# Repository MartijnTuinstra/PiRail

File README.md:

# PiRail
Raspberry Pi Rail Software

This software package is for a modeltrain enthusiasts that want to automate trains on their layout.
It is especially created for club layout that do not have specified order.

This package contains
- Board designs
- Firmware for the arduino's
- Software Engine
- Web interface
- Z21 Emulator & firmware for arduino

# Requirements

## Hardware

- 100MB storage space
- 100MB min RAM size
- 1GHz 2core ARM or better adviced

- Z21 Command Unit
- A Railway
- DCC trains

## Software

- PHP5
- wiringPi
- openssl

# Installation and Configuration

To build all the binaries and launch the Engine:
```
make
./baan
```

Use the config\_reader to edit or create modules
```
./config\_reader
```

To build and launch the Emulator:
```
cd Z21_Emulator
gcc emulator.c -std=c99 -lpthread -g -o Z21.out
./Z21.out
```

# Web interface

Make sure to drop the 'web' folder into your webserver. This package has no php webserver.

Browse to the index.php. This is the main interface.
From here you can:
- add/change train and so called Modules
- Control trains
- Control the layout

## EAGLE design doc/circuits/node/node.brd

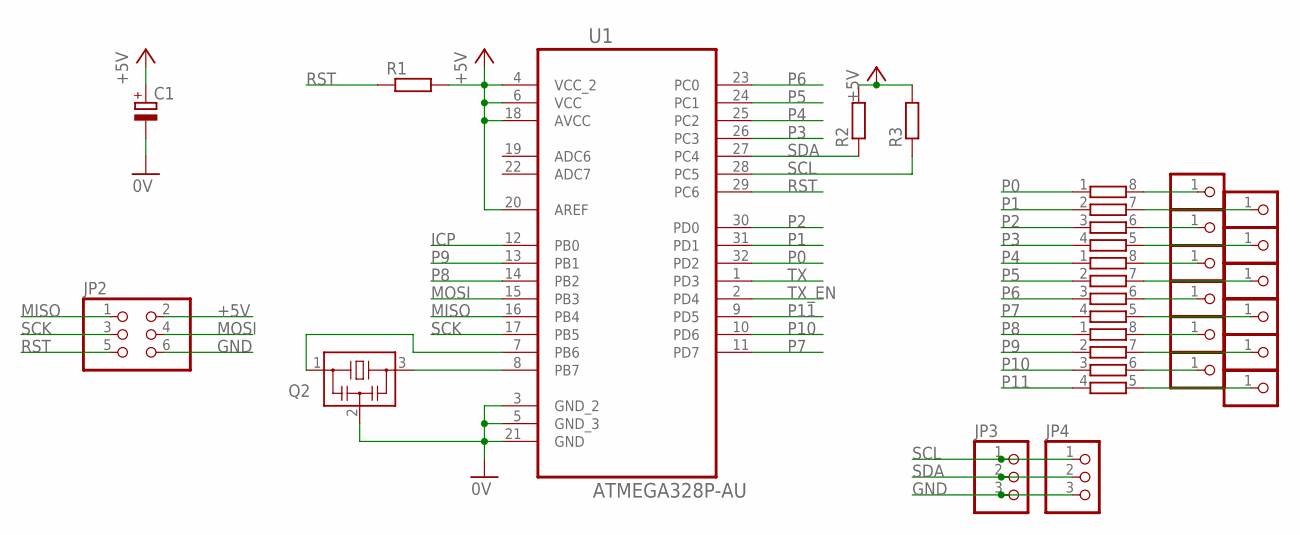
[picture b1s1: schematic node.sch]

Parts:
C1: CPOL-EU153CLV-0405; 153CLV-0405
JP1, JP6, JP7, JP8, JP9, JP10, JP11, JP12, JP13, JP14, JP15, JP16: PINHD-1X1; 1X01
JP2: PINHD-2X3; 2X03
JP3, JP4: PINHD-1X3; 1X03
Q2: CSTCR6M00G53Z; CSTCR6M
R1, R2, R3: R-EU_R0402; R0402
RN1, RN2, RN3: 4R-NEXB28V; EXB28V
U1: ATMEGA328P-AU; QFP80P900X900X120-32N

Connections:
+5V: C1.+, JP2.2, R1.2, R2.2, R3.2, U1.4 (VCC_2), U1.6 (VCC), U1.18 (AVCC), U1.20 (AREF)
GND: C1.-, JP2.6, JP3.3, JP4.3, Q2.2, U1.3 (GND_2), U1.5 (GND_3), U1.21 (GND)
ICP: U1.12 (PB0)
MISO: JP2.1, U1.16 (PB4)
MOSI: JP2.4, U1.15 (PB3)
unnamed: Q2.3, U1.8 (PB7)
unnamed: Q2.1, U1.7 (PB6)
unnamed: JP1.1, RN1.8 (2)
unnamed: JP16.1, RN1.7 (2)
unnamed: JP6.1, RN1.6 (2)
unnamed: JP15.1, RN1.5 (2)
unnamed: JP7.1, RN2.8 (2)
unnamed: JP14.1, RN2.7 (2)
unnamed: JP8.1, RN2.6 (2)
unnamed: JP13.1, RN2.5 (2)
unnamed: JP9.1, RN3.8 (2)
unnamed: JP12.1, RN3.7 (2)
unnamed: JP10.1, RN3.6 (2)
unnamed: JP11.1, RN3.5 (2)
P0: RN1.1, U1.32 (PD2)
P1: RN1.2 (1), U1.31 (PD1)
P2: RN1.3 (1), U1.30 (PD0)
P3: RN1.4 (1), U1.26 (PC3)
P4: RN2.1, U1.25 (PC2)
P5: RN2.2 (1), U1.24 (PC1)
P6: RN2.3 (1), U1.23 (PC0)
P7: RN2.4 (1), U1.11 (PD7)
P8: RN3.1, U1.14 (PB2)
P9: RN3.2 (1), U1.13 (PB1)
P10: RN3.3 (1), U1.10 (PD6)
P11: RN3.4 (1), U1.9 (PD5)
RST: JP2.5, R1.1, U1.29 (PC6)
SCK: JP2.3, U1.17 (PB5)
SCL: JP3.1, JP4.1, R3.1, U1.28 (PC5)
SDA: JP3.2, JP4.2, R2.1, U1.27 (PC4)
TX: U1.1 (PD3)
TX_EN: U1.2 (PD4)

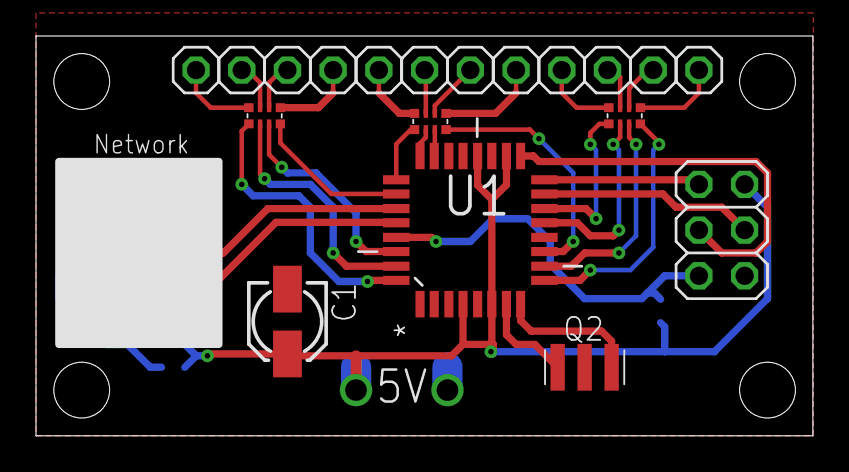
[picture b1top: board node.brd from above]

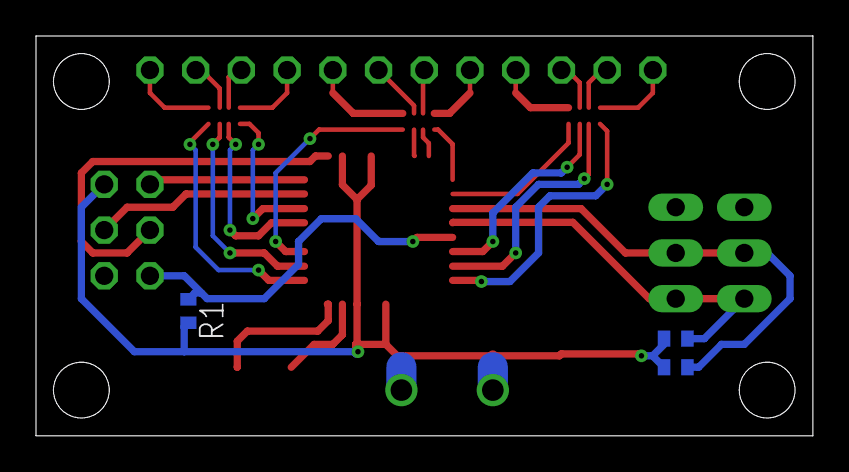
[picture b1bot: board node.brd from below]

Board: 2 copper layers, 43.2 x 22.2 mm, 24 parts (3 on the bottom side), 34 nets.

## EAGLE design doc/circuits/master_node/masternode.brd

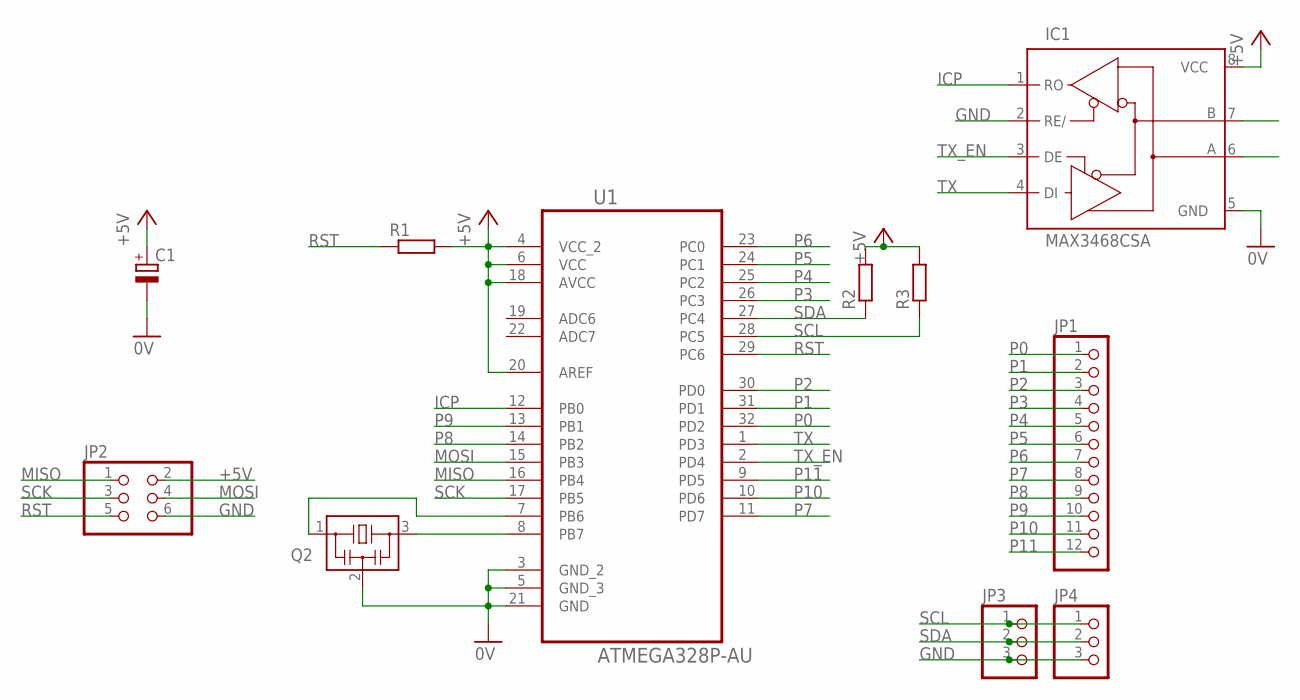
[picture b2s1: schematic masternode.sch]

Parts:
C1: CPOL-EU153CLV-0405; 153CLV-0405
IC1: MAX3468CSA; SO08
JP1: PINHD-1X12; 1X12
JP2: PINHD-2X3; 2X03
JP3, JP4: PINHD-1X3; 1X03
Q2: CSTCR6M00G53Z; CSTCR6M
R1, R2, R3: R-EU_R0402; R0402
U1: ATMEGA328P-AU; QFP80P900X900X120-32N

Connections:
+5V: C1.+, IC1.8 (VCC), JP2.2, R1.2, R2.2, R3.2, U1.4 (VCC_2), U1.6 (VCC), U1.18 (AVCC), U1.20 (AREF)
A: IC1.6 (A)
B: IC1.7 (B)
GND: C1.-, IC1.2 (RE/), IC1.5 (GND), JP2.6, JP3.3, JP4.3, Q2.2, U1.3 (GND_2), U1.5 (GND_3), U1.21 (GND)
ICP: IC1.1 (RO), U1.12 (PB0)
MISO: JP2.1, U1.16 (PB4)
MOSI: JP2.4, U1.15 (PB3)
unnamed: Q2.3, U1.8 (PB7)
unnamed: Q2.1, U1.7 (PB6)
P0: JP1.1, U1.32 (PD2)
P1: JP1.2, U1.31 (PD1)
P2: JP1.3, U1.30 (PD0)
P3: JP1.4, U1.26 (PC3)
P4: JP1.5, U1.25 (PC2)
P5: JP1.6, U1.24 (PC1)
P6: JP1.7, U1.23 (PC0)
P7: JP1.8, U1.11 (PD7)
P8: JP1.9, U1.14 (PB2)
P9: JP1.10, U1.13 (PB1)
P10: JP1.11, U1.10 (PD6)
P11: JP1.12, U1.9 (PD5)
RST: JP2.5, R1.1, U1.29 (PC6)
SCK: JP2.3, U1.17 (PB5)
SCL: JP3.1, JP4.1, R3.1, U1.28 (PC5)
SDA: JP3.2, JP4.2, R2.1, U1.27 (PC4)
TX: IC1.4 (DI), U1.1 (PD3)
TX_EN: IC1.3 (DE), U1.2 (PD4)

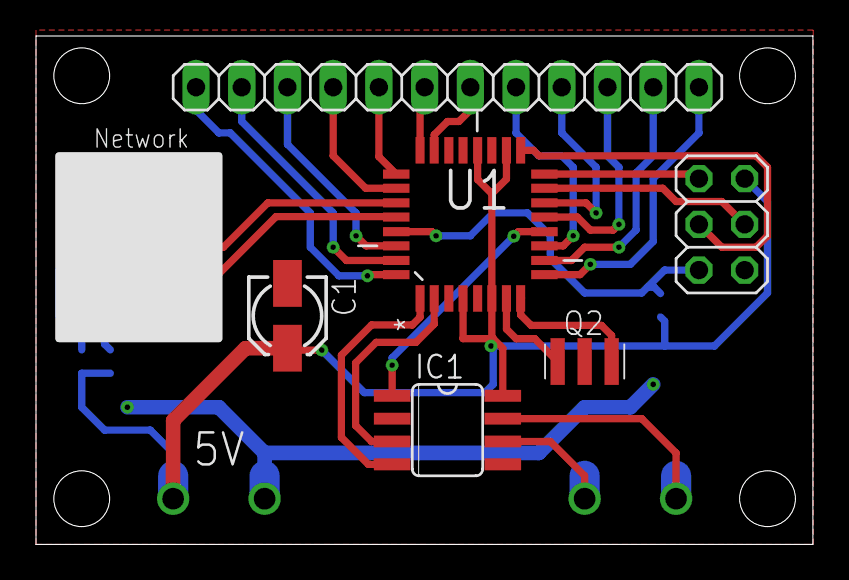
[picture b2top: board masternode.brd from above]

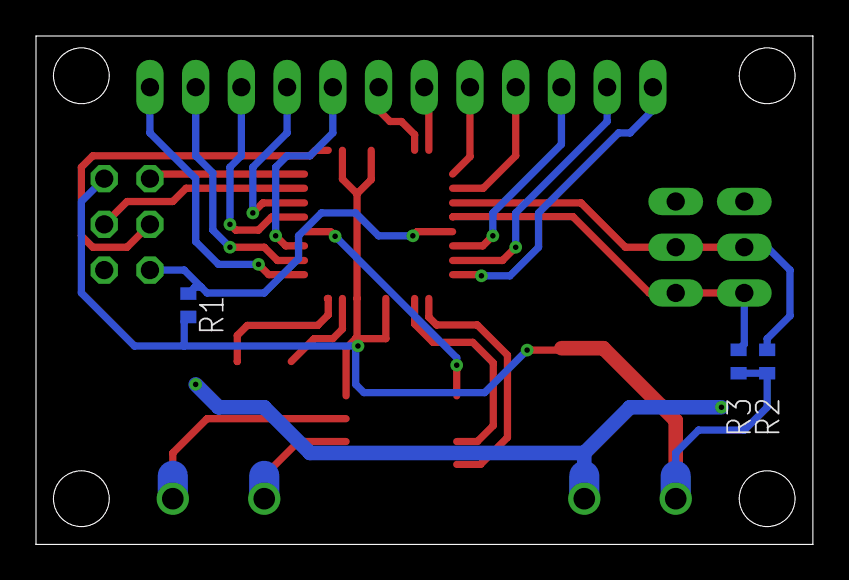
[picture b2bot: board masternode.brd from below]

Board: 2 copper layers, 43.2 x 28.2 mm, 11 parts (3 on the bottom side), 25 nets.

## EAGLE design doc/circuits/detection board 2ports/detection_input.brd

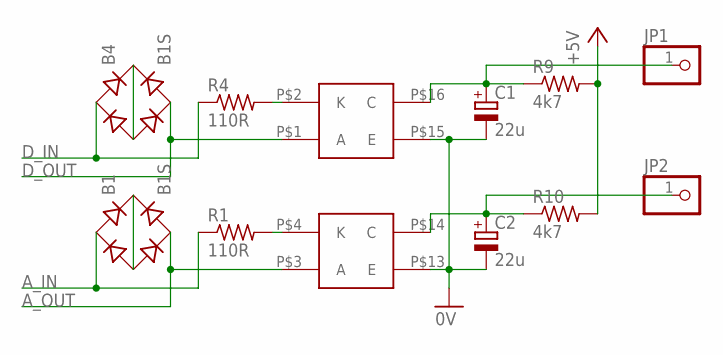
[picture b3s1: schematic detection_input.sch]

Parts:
B1, B4: B1S; MBS
C1, C2: 22u; E2-4
JP1, JP2: PINHD-1X1; 1X01
R1, R4: 110R; R0805
R9, R10: 4k7; R0805
U$1: ILQ620D

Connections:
0V: C1.-, C2.-, U$1.P$13 (E), U$1.P$15 (E)
+5V: R9.2, R10.2
A: C1.+, JP1.1, R9.1, U$1.P$16 (C)
A_IN: B1.AC1, R1.1
A_OUT: B1.AC2, U$1.P$3 (A)
B: C2.+, JP2.1, R10.1, U$1.P$14 (C)
D_IN: B4.AC1, R4.1
D_OUT: B4.AC2, U$1.P$1 (A)
unnamed: B1.+, B1.-
unnamed: R1.2, U$1.P$4 (K)
unnamed: R4.2, U$1.P$2 (K)
unnamed: B4.+, B4.-

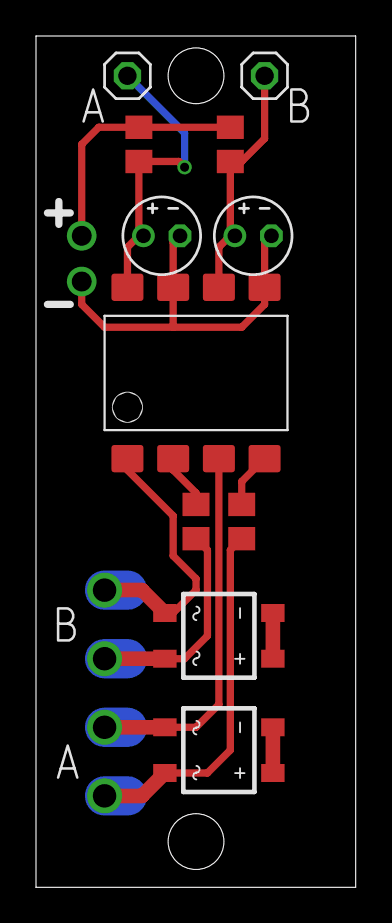
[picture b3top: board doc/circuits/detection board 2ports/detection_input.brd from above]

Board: 2 copper layers, 17.8 x 47.3 mm, 11 parts (0 on the bottom side), 12 nets.

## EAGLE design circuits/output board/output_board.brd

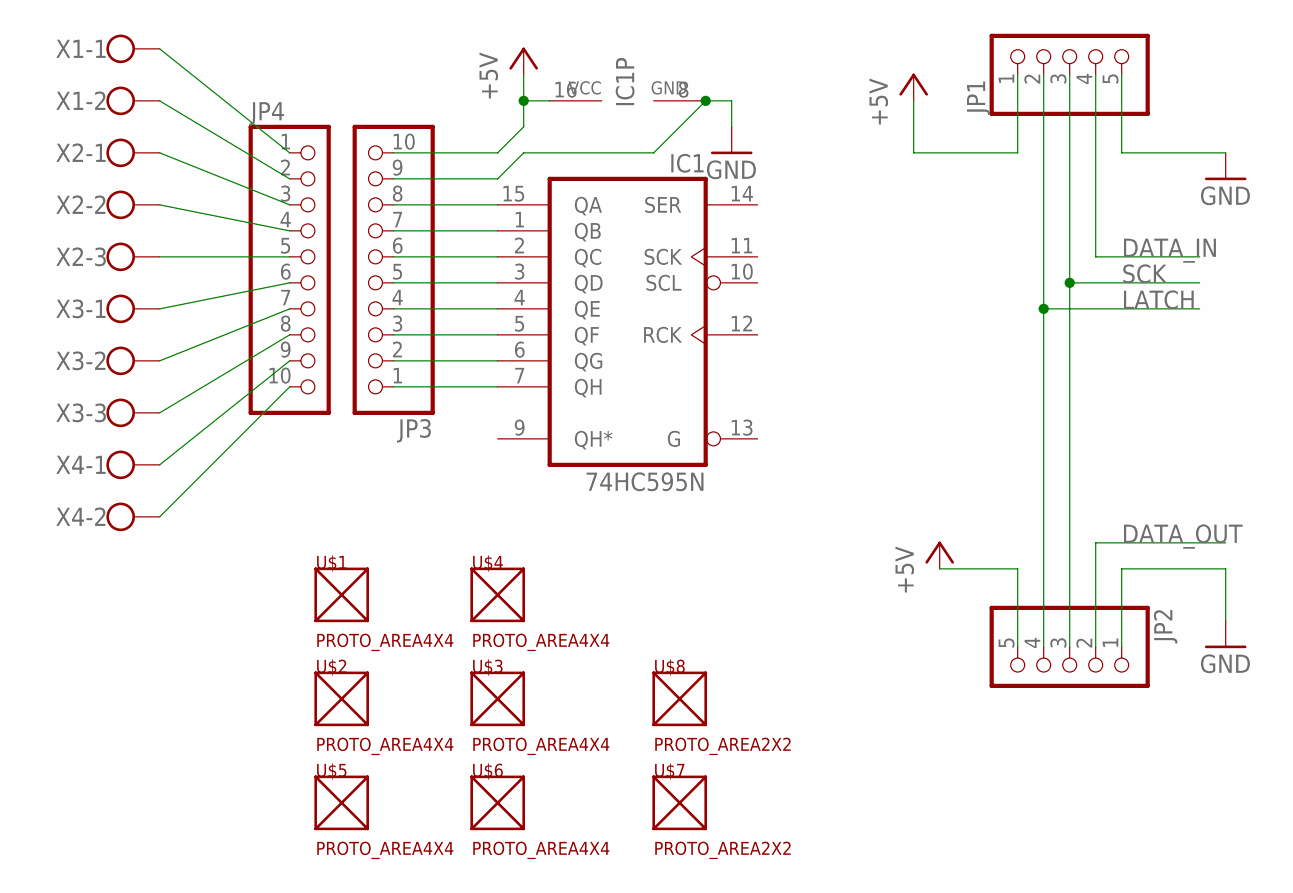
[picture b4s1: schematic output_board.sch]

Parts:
IC1: 74HC595N; DIL16
JP1, JP2: PINHD-1X5; 1X05
JP3, JP4: PINHD-1X10; 1X10
U$1, U$2, U$3, U$4, U$5, U$6: PROTO_AREA4X4; PROTO4X4
U$7, U$8: PROTO_AREA2X2; PROTO2X2
X1, X4: W237-102
X2, X3: W237-103

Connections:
+5V: IC1.16 (VCC), JP1.1, JP2.5, JP3.10
DATA_IN: JP1.4
DATA_OUT: JP2.2
GND: IC1.8 (GND), JP1.5, JP2.1, JP3.9
LATCH: JP1.2, JP2.4
unnamed: IC1.7 (QH), JP3.1
unnamed: IC1.6 (QG), JP3.2
unnamed: IC1.5 (QF), JP3.3
unnamed: IC1.4 (QE), JP3.4
unnamed: IC1.3 (QD), JP3.5
unnamed: IC1.2 (QC), JP3.6
unnamed: IC1.1 (QB), JP3.7
unnamed: IC1.15 (QA), JP3.8
unnamed: JP4.1, X1.1
unnamed: JP4.2, X1.2
unnamed: JP4.3, X2.1
unnamed: JP4.4, X2.2
unnamed: JP4.5, X2.3
unnamed: JP4.6, X3.1
unnamed: JP4.7, X3.2
unnamed: JP4.8, X3.3
unnamed: JP4.9, X4.1
unnamed: JP4.10, X4.2
SCK: JP1.3, JP2.3

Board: 2 copper layers, 17 parts (0 on the bottom side), 22 nets, no tracks yet.

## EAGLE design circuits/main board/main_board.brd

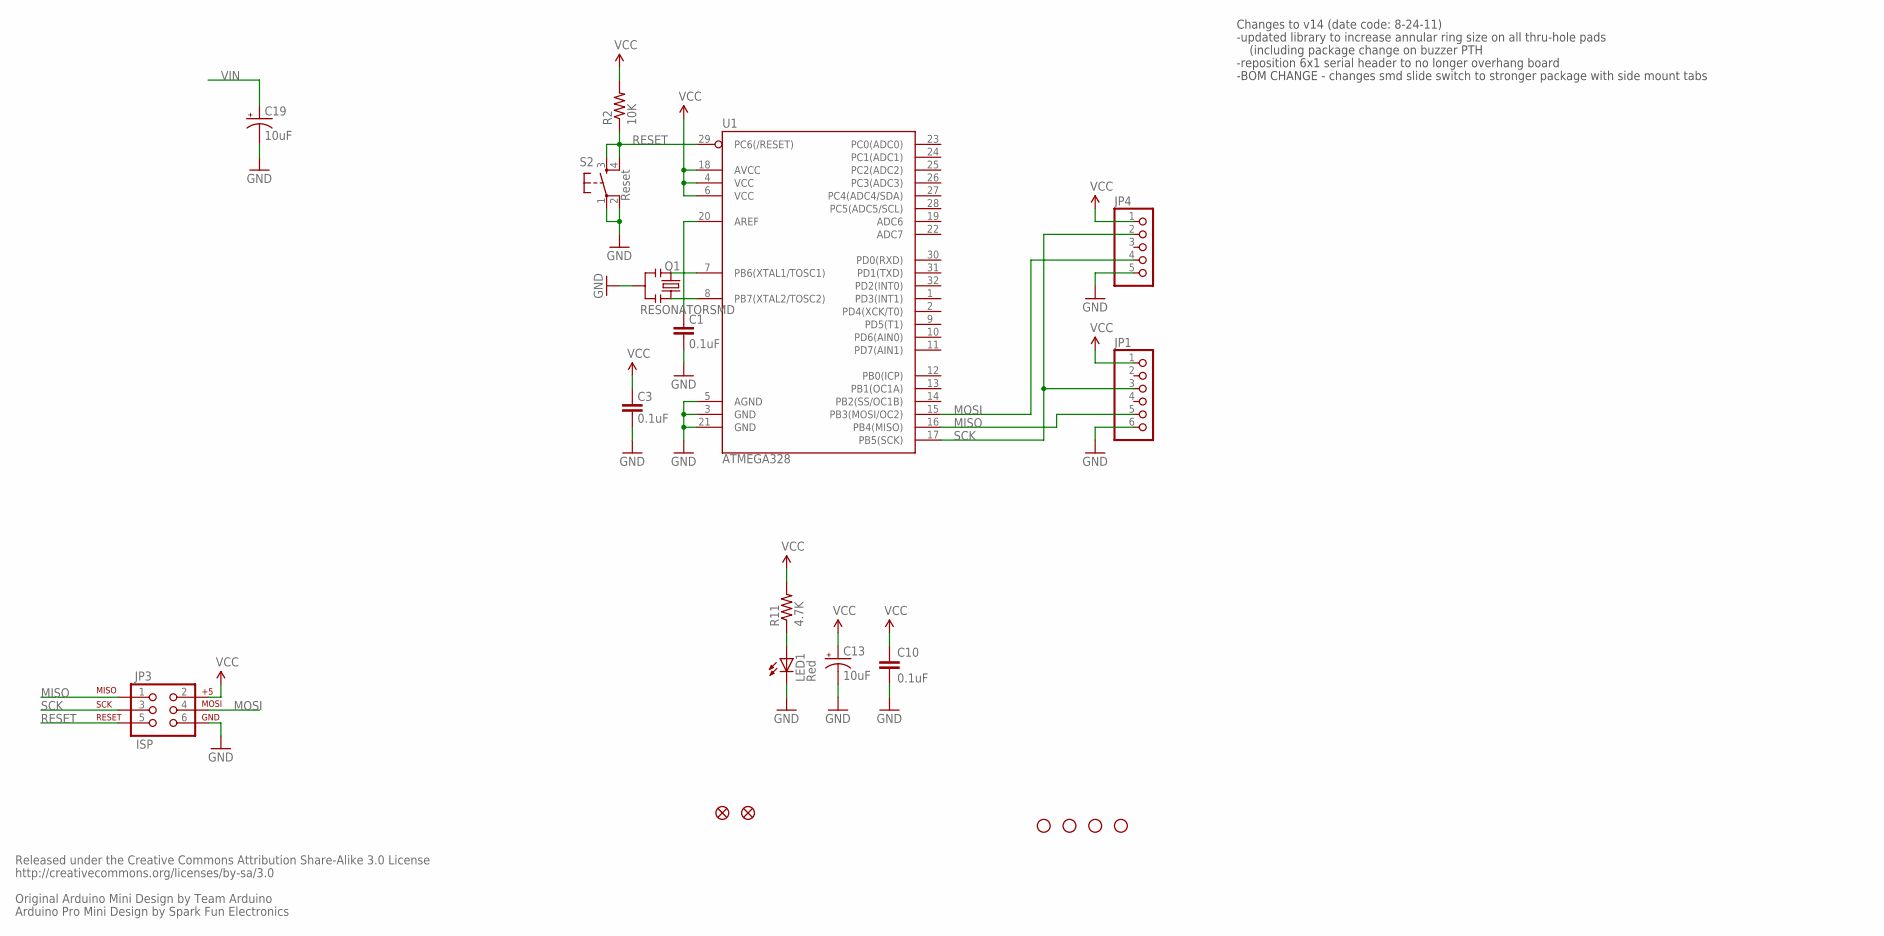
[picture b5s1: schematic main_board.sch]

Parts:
C1, C3, C10: 0.1uF; 0402-CAP
C13, C19: 10uF; EIA3216
JP1: PINHD-1X6; 1X06
JP2, JP5: FIDUCIAL1X2.5; FIDUCIAL-1X2.5
JP3: ISP; 2X3
JP4: PINHD-1X5; 1X05
LED1: Red; LED-0603
Q1: RESONATORSMD; RESONATOR-SMD
R2: 10K; 0402-RES
R11: 4.7K; 0402-RES
S2: Reset; TACTILE_SWITCH_SMD
U1: ATMEGA328; TQFP32-08
U$1, U$3, U$9, U$10: STAND-OFF

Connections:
AREF: C1.2, U1.20 (AREF)
GND: C1.1, C3.1, C10.2, C13.C (-), C19.C (-), JP1.6, JP3.6, JP4.5, LED1.C, Q1.2, S2.1, S2.2, U1.3 (GND), U1.5 (AGND), U1.21 (GND)
MISO: JP1.5, JP3.1, U1.16 (PB4(MISO))
MOSI: JP3.4, JP4.4, U1.15 (PB3(MOSI/OC2))
unnamed: Q1.1, U1.8 (PB7(XTAL2/TOSC2))
unnamed: Q1.3, U1.7 (PB6(XTAL1/TOSC1))
unnamed: LED1.A, R11.1
RESET: JP3.5, R2.1, S2.3, S2.4, U1.29 (PC6(/RESET))
SCK: JP1.3, JP3.3, JP4.2, U1.17 (PB5(SCK))
VCC: C3.2, C10.1, C13.A (+), JP1.1, JP3.2, JP4.1, R2.2, R11.2, U1.4 (VCC), U1.6 (VCC), U1.18 (AVCC)
VIN: C19.A (+)

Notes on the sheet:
Released under the Creative Commons Attribution Share-Alike 3.0 License
http://creativecommons.org/licenses/by-sa/3.0
Original Arduino Mini Design by Team Arduino
Arduino Pro Mini Design by Spark Fun Electronics
Changes to v14 (date code: 8-24-11)
-updated library to increase annular ring size on all thru-hole pads
-reposition 6x1 serial header to no longer overhang board
-BOM CHANGE - changes smd slide switch to stronger package with side mount tabs
(including package change on buzzer PTH

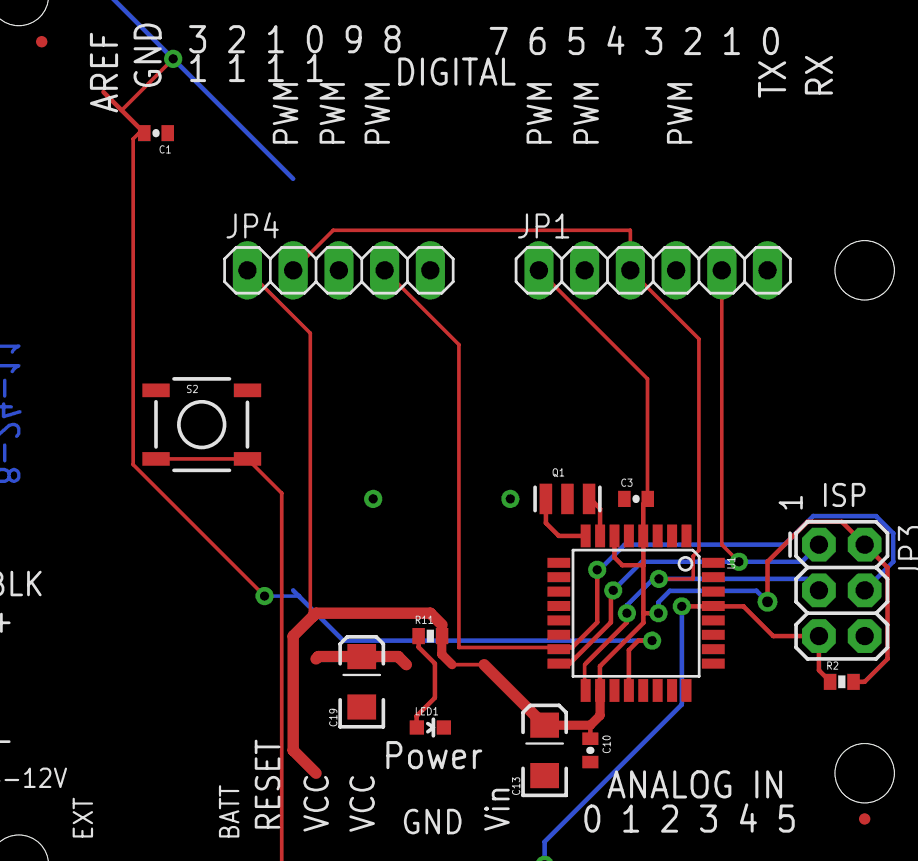
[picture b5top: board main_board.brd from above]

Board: 2 copper layers, 20 parts (0 on the bottom side), 10 nets.

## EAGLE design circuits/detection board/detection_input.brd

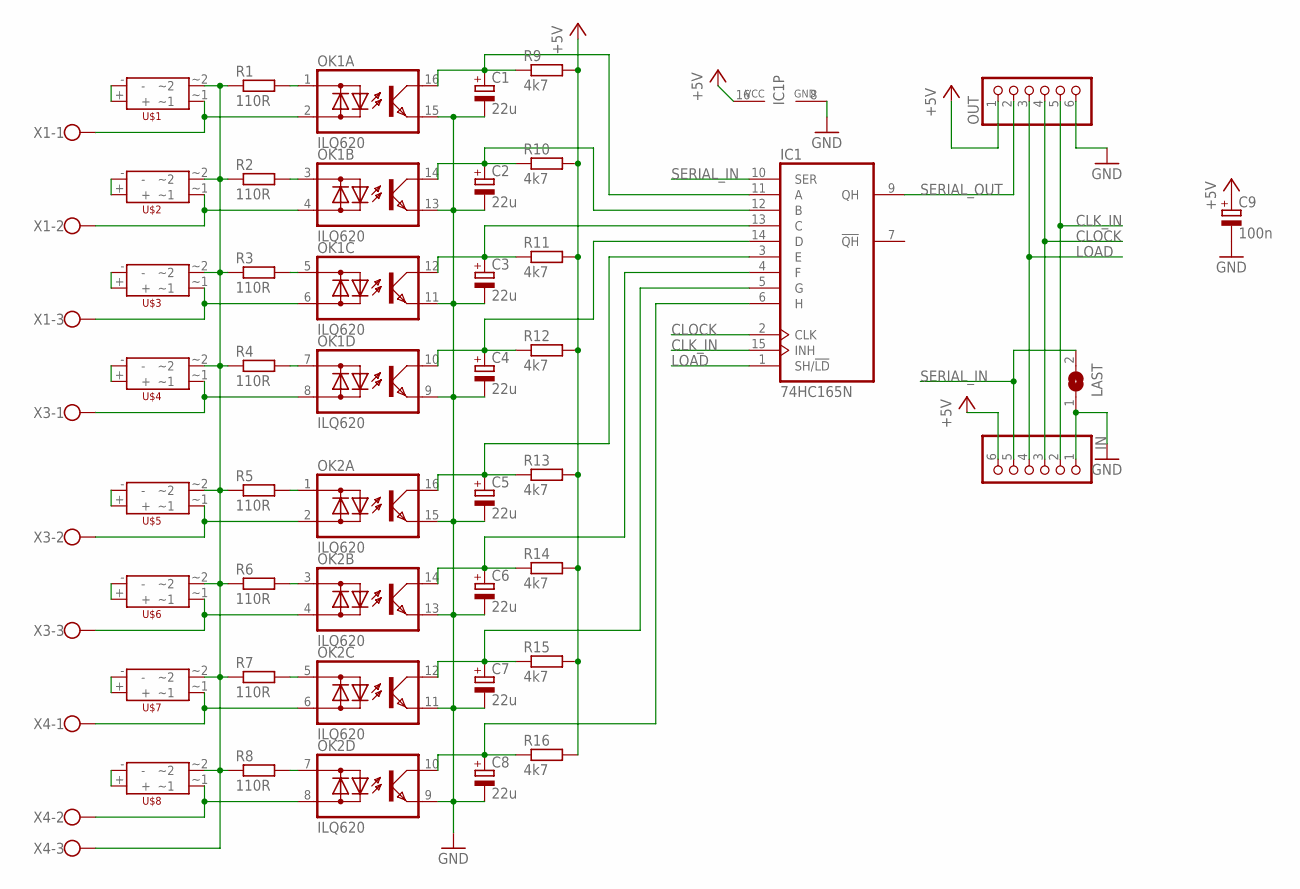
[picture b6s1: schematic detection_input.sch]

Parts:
C1, C2, C3, C4, C5, C6, C7, C8: 22u; E2-4
C9: 100n; A/3216-18W
IC1: 74HC165N; DIL16
IN: PINHD-1X6; 1X06
LAST: SJ
OK1, OK2: ILQ620; DIL16
OUT: PINHD-1X6; 1X06
R1, R2, R3, R4, R5, R6, R7, R8: 110R; 0204/7
R9, R10, R11, R12, R13, R14, R15, R16: 4k7; 0204/7
U$1, U$2, U$3, U$4, U$5, U$6, U$7, U$8: 2W10
X1, X3, X4: W237-103

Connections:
+5V: C9.+, IC1.16 (VCC), IN.6, OUT.1, R9.2, R10.2, R11.2, R12.2, R13.2, R14.2, R15.2, R16.2
CLK_IN: IC1.15 (INH), IN.2, OUT.5
CLOCK: IC1.2 (CLK), IN.3, OUT.4
GND: C1.-, C2.-, C3.-, C4.-, C5.-, C6.-, C7.-, C8.-, C9.-, IC1.8 (GND), IN.1, LAST.1, OK1.9 (E), OK1.11 (E), OK1.13 (E), OK1.15 (E), OK2.9 (E), OK2.11 (E), OK2.13 (E), OK2.15 (E), OUT.6
LOAD: IC1.1 (SH/!LD), IN.4, OUT.3
unnamed: U$1.+, U$1.-
unnamed: OK1.7 (AC1), R4.2
unnamed: OK1.5 (AC1), R3.2
unnamed: OK1.2 (AC2), U$1.~1, X1.1
unnamed: U$2.+, U$2.-
unnamed: OK1.3 (AC1), R2.2
unnamed: OK1.1 (AC1), R1.2
unnamed: OK1.4 (AC2), U$2.~1, X1.2
unnamed: U$3.+, U$3.-
unnamed: OK2.7 (AC1), R8.2
unnamed: OK2.5 (AC1), R7.2
unnamed: OK1.6 (AC2), U$3.~1, X1.3
unnamed: U$4.+, U$4.-
unnamed: OK2.3 (AC1), R6.2
unnamed: OK1.8 (AC2), U$4.~1, X3.1
unnamed: U$5.+, U$5.-
unnamed: R1.1, R2.1, R3.1, R4.1, R5.1, R6.1, R7.1, R8.1, U$1.~2, U$2.~2, U$3.~2, U$4.~2, U$5.~2, U$6.~2, U$7.~2, U$8.~2, X4.3
unnamed: OK2.1 (AC1), R5.2
unnamed: OK2.2 (AC2), U$5.~1, X3.2
unnamed: U$6.+, U$6.-
unnamed: C8.+, IC1.6 (H), OK2.10 (C), R16.1
unnamed: OK2.4 (AC2), U$6.~1, X3.3
unnamed: U$7.+, U$7.-
unnamed: C7.+, IC1.5 (G), OK2.12 (C), R15.1
unnamed: C6.+, IC1.4 (F), OK2.14 (C), R14.1
unnamed: OK2.6 (AC2), U$7.~1, X4.1
unnamed: U$8.+, U$8.-
unnamed: C5.+, IC1.3 (E), OK2.16 (C), R13.1
unnamed: OK2.8 (AC2), U$8.~1, X4.2
unnamed: C4.+, IC1.14 (D), OK1.10 (C), R12.1
unnamed: C3.+, IC1.13 (C), OK1.12 (C), R11.1
unnamed: C2.+, IC1.12 (B), OK1.14 (C), R10.1
unnamed: C1.+, IC1.11 (A), OK1.16 (C), R9.1
SERIAL_IN: IC1.10 (SER), IN.5, LAST.2
SERIAL_OUT: IC1.9 (QH), OUT.2

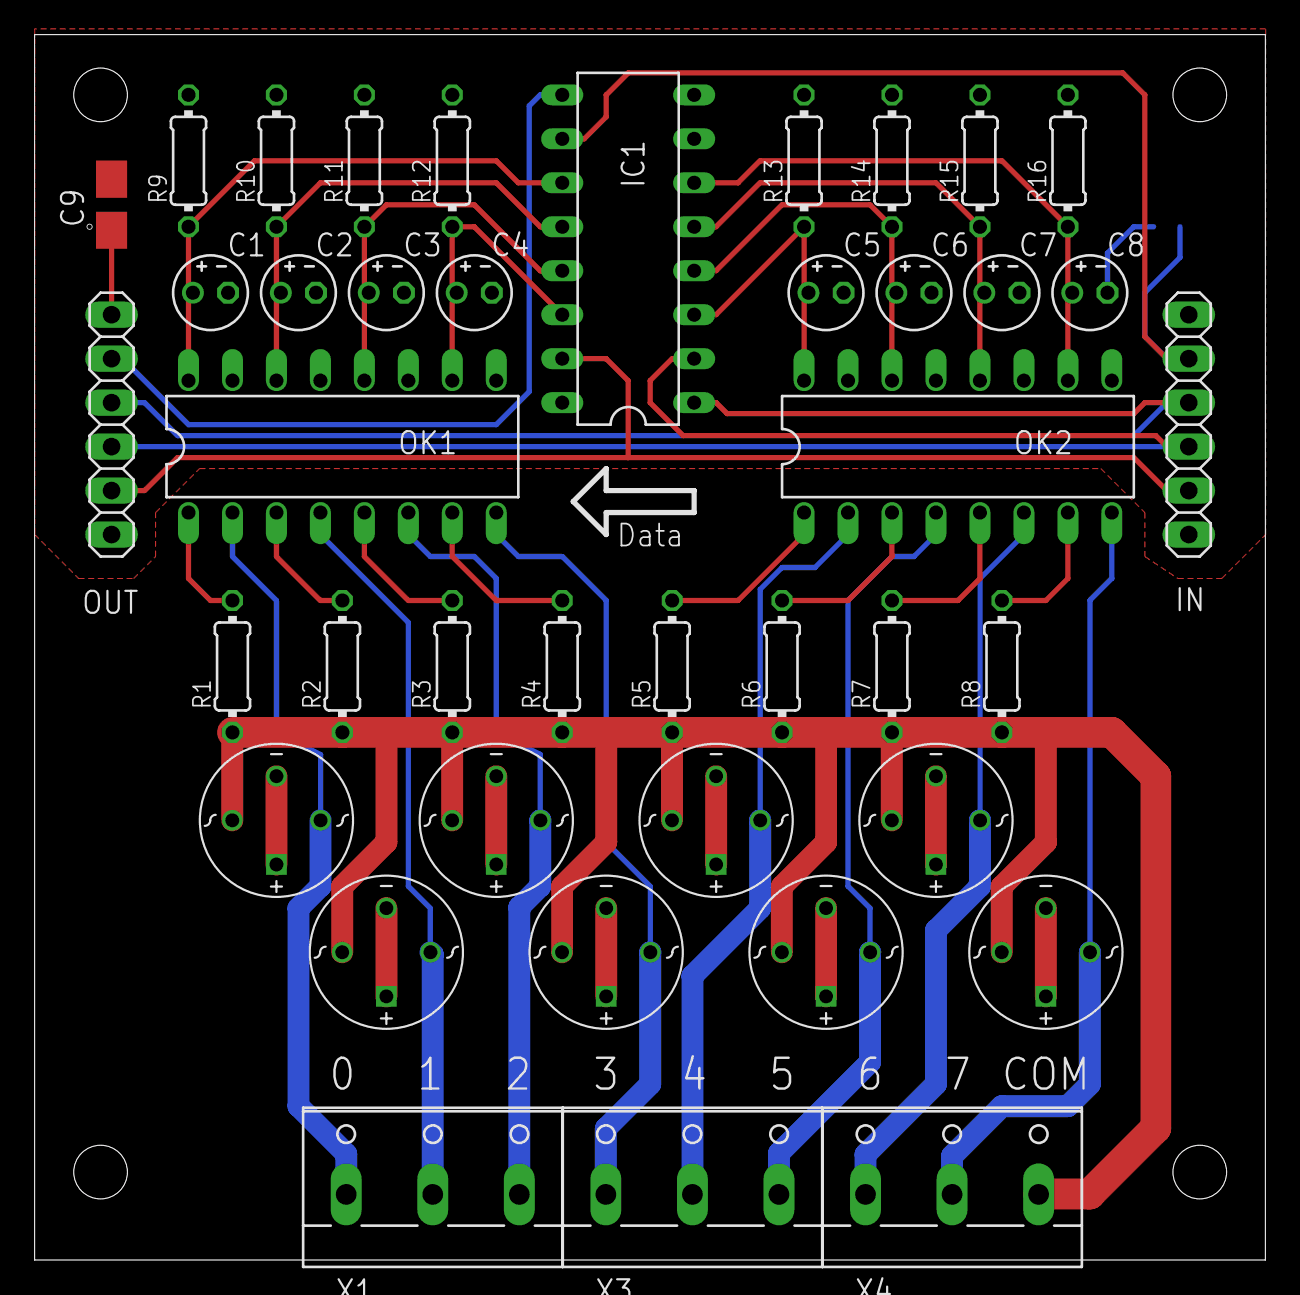
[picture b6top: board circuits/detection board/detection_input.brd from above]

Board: 2 copper layers, 71.1 x 70.8 mm, 42 parts (1 on the bottom side), 40 nets.

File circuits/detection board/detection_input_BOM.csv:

Qty;Total Qty;Value;Device;Package;Parts;Description;;;;;;;;;;;;;;;;;;;;;;;;;;;;
2;2;;PINHD-1X6;1X06;IN, OUT;;;;;;;;;;;;;;;;;;;;;;;;;;;;;
3;3;3pin Screw;W237-103;W237-103;X1, X3, X4;;;;;;;;;;;;;;;;;;;;;;;;;;;;;
1;1;100n;CPOL-EUA/3216-18W;A/3216-18W;C9;;;;;;;;;;;;;;;;;;;;;;;;;;;;;
8;8;110R;R0204/7;0204/7;R1, R2, R3, R4, R5, R6, R7, R8;;;;;;;;;;;;;;;;;;;;;;;;;;;;;
8;8;22u;CPOL-EUE2-4;E2-4;C1, C2, C3, C4, C5, C6, C7, C8;;;;;;;;;;;;;;;;;;;;;;;;;;;;;
8;8;2W10;2W10;2W10;U$1, U$2, U$3, U$4, U$5, U$6, U$7, U$8;;;;;;;;;;;;;;;;;;;;;;;;;;;;;
8;8;4k7;R0204/7;0204/7;R9, R10, R11, R12, R13, R14, R15, R16;;;;;;;;;;;;;;;;;;;;;;;;;;;;;
1;1;74HC165N;74HC165N;DIL16;IC1;;;;;;;;;;;;;;;;;;;;;;;;;;;;;
2;2;ILQ620;ILQ620;DIL16;OK1, OK2;;;;;;;;;;;;;;;;;;;;;;;;;;;;;
3;3;16pin;DIP Socket;DIL16;IC1,OK1,OK2;;;;;;;;;;;;;;;;;;;;;;;;;;;;;
;;;;;;;;;;;;;;;;;;;;;;;;;;;;;;;;;;
;1;;;;;;;;;;;;;;;;;;;;;;;;;;;;;;;;;
Bocht;;;;;;;3-Rail 7 blocks;;;;;;;4-Rail 8 blocks;;;;;;;4-Rail 3 blocks;;;;;;;;4-Rail 3 blocks;;;;;
Qty;Total Qty;Value;Device;Package;Parts;;Qty;Total Qty;Value;Device;Package;Parts;;Qty;Total Qty;Value;Device;Package;Parts;;Qty;Total Qty;Value;Device;Package;Parts;;;;Total Qty;Value;Device;Package;Parts
2;4;;PINHD-1X6;1X06;IN, OUT;;2;4;;PINHD-1X6;1X06;IN, OUT;;2;4;;PINHD-1X6;1X06;IN, OUT;;2;4;;PINHD-1X6;1X06;IN, OUT;;;;16;;PINHD-1X6;1X06;IN, OUT
3;6;3pin Screw;W237-103;W237-103;X1, X3, X4;;3;6;3pin Screw;W237-103;W237-103;X1, X3, X4;;3;6;3pin Screw;W237-103;W237-103;X1, X3, X4;;3;6;3pin Screw;W237-103;W237-103;X1, X3, X4;;;;24;3pin Screw;W237-103;W237-103;X1, X3, X4
1;2;100n;CPOL-EUA/3216-18W;A/3216-18W;C9;;1;2;100n;CPOL-EUA/3216-18W;A/3216-18W;C9;;1;2;100n;CPOL-EUA/3216-18W;A/3216-18W;C9;;1;2;100n;CPOL-EUA/3216-18W;A/3216-18W;C9;;;;8;100n;CPOL-EUA/3216-18W;A/3216-18W;C9
4;8;110R;R0204/7;0204/7;R1, R2, R3, R4, R5, R6, R7, R8;;7;14;110R;R0204/7;0204/7;R1, R2, R3, R4, R5, R6, R7, R8;;8;16;110R;R0204/7;0204/7;R1, R2, R3, R4, R5, R6, R7, R8;;3;6;110R;R0204/7;0204/7;R1, R2, R3, R4, R5, R6, R7, R8;;;;44;110R;R0204/7;0204/7;R1, R2, R3, R4, R5, R6, R7, R8
4;8;22u;CPOL-EUE2-4;E2-4;C1, C2, C3, C4, C5, C6, C7, C8;;7;14;22u;CPOL-EUE2-4;E2-4;C1, C2, C3, C4, C5, C6, C7, C8;;8;16;22u;CPOL-EUE2-4;E2-4;C1, C2, C3, C4, C5, C6, C7, C8;;3;6;22u;CPOL-EUE2-4;E2-4;C1, C2, C3, C4, C5, C6, C7, C8;;;;44;22u;CPOL-EUE2-4;E2-4;C1, C2, C3, C4, C5, C6, C7, C8
4;8;2W10;2W10;2W10;U$1, U$2, U$3, U$4, U$5, U$6, U$7, U$8;;7;14;2W10;2W10;2W10;U$1, U$2, U$3, U$4, U$5, U$6, U$7, U$8;;8;16;2W10;2W10;2W10;U$1, U$2, U$3, U$4, U$5, U$6, U$7, U$8;;3;6;2W10;2W10;2W10;U$1, U$2, U$3, U$4, U$5, U$6, U$7, U$8;;;;44;2W10;2W10;2W10;U$1, U$2, U$3, U$4, U$5, U$6, U$7, U$8
4;8;4k7;R0204/7;0204/7;R9, R10, R11, R12, R13, R14, R15, R16;;7;14;4k7;R0204/7;0204/7;R9, R10, R11, R12, R13, R14, R15, R16;;8;16;4k7;R0204/7;0204/7;R9, R10, R11, R12, R13, R14, R15, R16;;3;6;4k7;R0204/7;0204/7;R9, R10, R11, R12, R13, R14, R15, R16;;;;44;4k7;R0204/7;0204/7;R9, R10, R11, R12, R13, R14, R15, R16
1;2;74HC165N;74HC165N;DIL16;IC1;;1;2;74HC165N;74HC165N;DIL16;IC1;;1;2;74HC165N;74HC165N;DIL16;IC1;;1;2;74HC165N;74HC165N;DIL16;IC1;;;;8;74HC165N;74HC165N;DIL16;IC1
1;2;ILQ620;ILQ620;DIL16;OK1, OK2;;2;4;ILQ620;ILQ620;DIL16;OK1, OK2;;2;4;ILQ620;ILQ620;DIL16;OK1, OK2;;1;2;ILQ620;ILQ620;DIL16;OK1, OK2;;;;12;ILQ620;ILQ620;DIL16;OK1, OK2
2;4;16pin;DIP Socket;DIL16;IC1,OK1,OK2;;3;6;16pin;DIP Socket;DIL16;IC1,OK1,OK2;;3;6;16pin;DIP Socket;DIL16;IC1,OK1,OK2;;2;4;16pin;DIP Socket;DIL16;IC1,OK1,OK2;;;;20;16pin;DIP Socket;DIL16;IC1,OK1,OK2
;;;;;;;;;;;;;;;;;;;;;;;;;;;;;;;;;;
;2;;;;;;;2;;;;;;;2;;;;;;;2;;;;;;;;8;;;;

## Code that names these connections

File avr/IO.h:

#ifndef INCLUDED_IO_H
#define INCLUDED_IO_H

#include "prgmem.h"
#include "avr/interrupt.h"

#define PORT_(port) PORT ## port
#define DDR_(port)  DDR  ## port
#define PIN_(port)  PIN  ## port

#define PORT(port) PORT_(port)
#define DDR(port)  DDR_(port)
#define PIN(port)  PIN_(port)

#define _set_in(PORT, PIN) PORT &= ~(1 << PIN)
#define _set_out(PORT, PIN)  PORT |= (1<< PIN)

#define _set_high(PORT, PIN) PORT |= (1 << PIN)
#define _set_low(PORT, PIN)  PORT &= ~(1<< PIN)
#define _set_toggle(PORT, PIN) PORT ^= (1 << PIN)
#define _read_pin(PORT, PIN)     PORT & (1 << PIN)

void set_out(uint8_t pin);
void set_in(uint8_t pin);

void set_high(uint8_t pin);
void set_low(uint8_t pin);
void set_toggle(uint8_t pin);

uint8_t read(uint8_t pin);

// enum IO_type {
// 	IO_InputToggle,
// 	IO_InputRising,
// 	IO_InputFalling,
// 	IO_Output
// };

#define HOLDDELAY      8
#define REPRESSDELAY   16

enum e_IO_type {
  IO_Undefined,
  IO_Output,
  IO_Output_Blink,
  IO_Output_Servo,
  IO_Output_PWM,
  IO_Input,
  IO_Input_Block,
  IO_Input_Switch,
  IO_Input_MSSwitch,
};

enum e_IO_output_event {
  IO_event_Low,
  IO_event_High,
  IO_event_Pulse,
  IO_event_Toggle
};

enum e_IO_blink_event {
  IO_event_B_Low,
  IO_event_B_High,
  IO_event_Blink1,
  IO_event_Blink2
};

enum e_IO_servo_event {
  IO_event_Servo1,
  IO_event_Servo2,
  IO_event_Servo3,
  IO_event_Servo4
};

enum e_IO_PWM_event {
  IO_event_PWM1,
  IO_event_PWM2,
  IO_event_PWM3,
  IO_event_PWM4
};

union u_IO_event {
  enum e_IO_output_event output;
  enum e_IO_blink_event blink;
  enum e_IO_servo_event servo;
  enum e_IO_PWM_event pwm;

  uint8_t value;
};

#define PA 0
#define PB 1
#define PC 2
#define PD 3
#define PE 4
#define PF 5
#define PG 6
#define PH 7
#define PJ 8
#define PK 7
#define PL 8

#define pgm_read_word(address_short) __LPM_word((uint16_t)(address_short))

#define portOutputRegister(P) ( (volatile uint8_t *)( pgm_read_word( _PORT + (P))) )
#define portModeRegister(P) ( (volatile uint8_t *)( pgm_read_word( _DDR + (P))) )
#define portInputRegister(P) ( (volatile uint8_t *)( pgm_read_word( _PIN + (P))) )

#define _portOutputRegister(P) ( (volatile uint8_t *)( pgm_read_word( portlist + (P))) )
#define _portModeRegister(P) ( (volatile uint8_t *)( pgm_read_word( ddrlist + (P))) )
#define _portInputRegister(P) ( (volatile uint8_t *)( pgm_read_word( pinlist + (P))) )

// extern const uint16_t PROGMEM _PORT[];

// extern const uint16_t PROGMEM _DDR[];

// extern const uint16_t PROGMEM _PIN[];

// extern uint8_t pin_to_Port[];

// extern uint8_t pin_to_BIT[];

#ifndef IO_SPI

const uint16_t PROGMEM portlist[] = {
	#if defined(__AVR_ATmega64A__) || defined(__AVR_ATmega2560__)
	(uint16_t) &PORTA,
	#endif
	(uint16_t) &PORTB,
	(uint16_t) &PORTC,
	(uint16_t) &PORTD,
	#if defined(__AVR_ATmega64A__) || defined(__AVR_ATmega2560__)
	(uint16_t) &PORTE,
	(uint16_t) &PORTF,
	#endif
	#if defined(__AVR_ATmega64A__)
	(uint16_t) &PORTG,
	#elif defined(__AVR_ATmega2560__)
	(uint16_t) &PORTH,
	(uint16_t) &PORTJ,
	(uint16_t) &PORTK,
	(uint16_t) &PORTL,
	#endif
};
const uint16_t PROGMEM ddrlist[] = {
	#if defined(__AVR_ATmega64A__) || defined(__AVR_ATmega2560__)
	(uint16_t) &DDRA,
	#endif
	(uint16_t) &DDRB,
	(uint16_t) &DDRC,
	(uint16_t) &DDRD,
	#if defined(__AVR_ATmega64A__) || defined(__AVR_ATmega2560__)
	(uint16_t) &DDRE,
	(uint16_t) &DDRF,
	#endif
	#if defined(__AVR_ATmega64A__)
	(uint16_t) &DDRG,
	#elif defined(__AVR_ATmega2560__)
	(uint16_t) &DDRH,
	(uint16_t) &DDRJ,
	(uint16_t) &DDRK,
	(uint16_t) &DDRL,
	#endif
};
const uint16_t PROGMEM pinlist[] = {
	#if defined(__AVR_ATmega64A__) || defined(__AVR_ATmega2560__)
	(uint16_t) &PINA,
	#endif
	(uint16_t) &PINB,
	(uint16_t) &PINC,
	(uint16_t) &PIND,
	#if defined(__AVR_ATmega64A__) || defined(__AVR_ATmega2560__)
	(uint16_t) &PINE,
	(uint16_t) &PINF,
	#endif
	#if defined(__AVR_ATmega64A__)
	(uint16_t) &PING,
	#elif defined(__AVR_ATmega2560__)
	(uint16_t) &PINH,
	(uint16_t) &PINJ,
	(uint16_t) &PINK,
	(uint16_t) &PINL,
	#endif
};

#if defined(__AVR_ATmega328__) || defined(__AVR_ATmega328P__)
	#define MAX_PORTS 3
	#define MAX_PINS 13
	// RNet uses B0,B1,B2 -> 0,1,2
	const uint8_t list[] = {
		// 0, 1, 2, 3, 4, 5
		// PD4, PD3, PD5, PD6, PD7, PD2
		20, 19, 21, 22, 23, 18,
		// 6, 7, 8, 9, 10, 11
		// PC5, PC4, PC3, PC2, PC1, PC0
		13, 12, 11, 10, 9, 8,
		// 12 // DEBUG
		// PB5
		5
	};
#elif defined(__AVR_ATmega64A__)
	#define MAX_PORTS 7
	#define MAX_PINS 40
	const uint8_t list[] = {
		// 0, 1 (PG)
		52, 51,
		// 2 (PB)
		15,
		// 3 (PD)
		24,
		// 4, 5, 6, 7 (PB)
		14, 13, 12, 8, 
		// 8, 9, 10, 11, 12, 13, 14, 15 (PE)
		39, 38, 37, 36, 35, 34, 33, 32,
		// 16, 17, 18, 19, 20, 21, 22, 23 (PF)
		40, 41, 42, 43, 44, 45, 46, 47,
		// 24, 25, 26, 27, 28, 29, 30, 31  (PA)
		0, 1, 2, 3, 4, 5, 6, 7,
		// 32, 33, 34, 35, 36, 37, 38, 39 (PC)
		16, 17, 18, 19, 20, 21, 22, 23
	};
#elif defined(__AVR_ATmega2560__)
	#define MAX_PORTS 10
	#define MAX_PINS 72

	const uint8_t list[] = {
		// 0, 1, 2, 3, 4, 5, 6, 7 (PE)
		39, 38, 37, 36, 35, 34, 33, 32, 
		// 8, 9, 10, 11, 12, 13, 14, 15 (PH)
		55, 54, 53, 52, 51, 50, 49, 48,
		// 16, 17, 18 (PD)
		31, 30, 29,
		// 19, 20, 21, 22, 23 (PB)
		8, 12, 13, 14, 15,
		// 24, 25, 26, 27, 28, 29, 30, 31 (PL)
		79, 78, 77, 76, 75, 74, 73, 72,
		// 32, 33, 34, 35, 36, 37, 38, 39 (PC)
		23, 22, 21, 20, 19, 18, 17, 16,
		// 40, 41, 42, 43, 44, 45, 46, 47 (PJ)
		63, 62, 61, 60, 59, 58, 57, 56,
		// 48, 49, 50, 51, 52, 53, 54, 55 (PA)
		0, 1, 2, 3, 4, 5, 6, 7,
		// 56, 57, 58, 59, 60, 61, 62, 63 (PK)
		64, 65, 66, 67, 68, 69, 70, 71,
		// 64, 65, 66, 67, 68, 69, 70, 71 (PF)
		40, 41, 42, 43, 44, 45, 46, 47,
	};
#endif

#else // IO_SPI
	#undef MAX_PORTS
	#define MAX_PORTS 6
	#define MAX_PINS 48*2
#endif

class IO {
	public:
		void set(uint8_t pin, union u_IO_event func);

		inline void high(uint8_t pin);
		inline void low(uint8_t pin);
		inline void toggle(uint8_t pin);
		inline void out(uint8_t pin);
		inline void in(uint8_t pin);
		inline uint8_t read(uint8_t pin);

		void init();
		void initPin(uint8_t pin);

		void blink1();
		void blink2();

		void pulse_high();
		void pulse_low();

		void servo_low();
		void servo_high(uint8_t * mask);

		void set_mask(uint8_t pin, uint8_t * mask);
		void unset_mask(uint8_t pin, uint8_t * mask);

		void readInput();
		void readInput(uint8_t *);
		void copyInput(uint8_t *);
		void copyInput();
		#ifdef IO_SPI
		void writeOutput();
		void readwrite();
		#endif

		uint8_t debounce(uint8_t *, uint8_t *);

		uint16_t calculateTimer(uint16_t mseconds);

		uint16_t blink1_period;
		volatile uint16_t blink1_counter;
		uint16_t blink2_period;
		volatile uint16_t blink2_counter;
		volatile uint16_t pulse_counter;
		uint16_t pulse_length;

		uint8_t servo1Pulse;
		volatile uint16_t servo1counter;
		uint8_t servo2Pulse;
		volatile uint16_t servo2counter;

		volatile uint8_t compareInt;
		// uint8_t servo3Pulse;
		// uint16_t servo3counter;
		// uint8_t servo4Pulse;
		// uint16_t servo4counter;
		
		uint8_t readData[MAX_PORTS];
		uint8_t oldreadData[MAX_PORTS];
		uint8_t readMask[MAX_PORTS];

  		uint8_t DebouncedData[MAX_PORTS];

		uint8_t holdState;
		uint8_t repressState;
		uint8_t HoldStates[MAX_PORTS][HOLDDELAY];
		uint8_t RepressStates[MAX_PORTS][REPRESSDELAY];

	// private:
		uint8_t blink1Mask[MAX_PORTS];
		uint8_t blink2Mask[MAX_PORTS];

		uint8_t pulseMask[MAX_PORTS];

		uint8_t invertedMask[MAX_PORTS];

		uint8_t servo1Mask[MAX_PORTS];
		uint8_t servo2Mask[MAX_PORTS];
		uint8_t servo3Mask[MAX_PORTS];
		uint8_t servo4Mask[MAX_PORTS];


		#ifdef IO_SPI
		uint8_t writeData[MAX_PORTS];
		enum e_IO_type typelist[MAX_PORTS*16];
		#else
		enum e_IO_type typelist[MAX_PINS];
		#endif
};


extern IO io;

#define IO_TIMER_REG TCNT0
#define IO_TIMER_PRESCALER (1 << CS02) | (1 << CS00)
#define IO_TIMER_OVERFLOW_INT TIMER0_OVF_vect

#if defined(__AVR_ATmega328__) || defined(__AVR_ATmega328P__) || defined(__AVR_ATmega2560__)

#define IO_TIMER TCCR0B
#define IO_TIMER_INT TIMSK0
#define IO_TIMER_OVERFLOW_INT_REG (1<<TOIE0) //TOIE
#define IO_TIMER_COMPA_INT_REG (1<<OCIE0A) //OCIEA


#define IO_TIMER_COMPA_REG OCR0A

#define IO_TIMER_COMPA_INT TIMER0_COMPA_vect

#else // __AVR_ATmega64A

#define IO_TIMER TCCR0
#define IO_TIMER_INT TIMSK
#define IO_TIMER_OVERFLOW_INT_REG (1 << TOIE0)
#define IO_TIMER_COMPA_INT_REG (1 << OCIE0)

#define IO_TIMER_COMPA_REG OCR0

#define IO_TIMER_COMPA_INT TIMER0_COMP_vect

#endif

#define IO_Enable_COMPA_INT IO_TIMER_INT |= IO_TIMER_COMPA_INT_REG
#define IO_Disable_COMPA_INT IO_TIMER_INT &= ~(IO_TIMER_COMPA_INT_REG)

#define IO_SERVO_MIN 15
#define IO_SERVO_MAX 32
#define IO_SERVO_PERIOD 313

#define IO_INT_BlinkA 0x01
#define IO_INT_BlinkB 0x02
#define IO_INT_Pulse  0x04
#define IO_INT_Servo  0x08
#define IO_INT_Servo1 0x10
#define IO_INT_Servo2 0x20
#define IO_INT_Servo3 0x40
#define IO_INT_Servo4 0x80

#endif

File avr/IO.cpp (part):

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#ifdef IO_SPI

#define LATCH_OUT_PORT PORTD
#define LATCH_OUT_PIN  PD3
#define LATCH_IN_PORT PORTC
#define LATCH_IN_PIN  PC0
#define LOAD_IN_PORT PORTC
#define LOAD_IN_PIN  PC2

#define LATCH_OUT_ENABLE  LATCH_OUT_PORT &= ~(1 << LATCH_OUT_PIN) // Low
#define LATCH_OUT_DISABLE LATCH_OUT_PORT |=  (1 << LATCH_OUT_PIN) // High
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	#if defined(__AVR_ATmega328__) || defined(__AVR_ATmega328P__)
	// set mosi and sck output
	// DDRB = (1<<DDB2)|(1<<DDB3)|(1<<DDB5);
	_set_out(DDR(B), PB5); //SCK
	_set_in(DDR(B),  PB4); //MISO
	_set_out(DDR(B), PB3); //MOSI
	_set_out(DDR(B), PB2); //SS

	_set_out(DDR(D), LATCH_OUT_PIN);
	_set_out(DDR(C), LATCH_IN_PIN);
	_set_out(DDR(C), LOAD_IN_PIN);

	_set_high(PORT(B), PB2); //SS

	#else

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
